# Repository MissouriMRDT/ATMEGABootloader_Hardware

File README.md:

# ATMEGABootloader_Hardware
A bootloader shield to flash an ATMEGA328 on an arduino

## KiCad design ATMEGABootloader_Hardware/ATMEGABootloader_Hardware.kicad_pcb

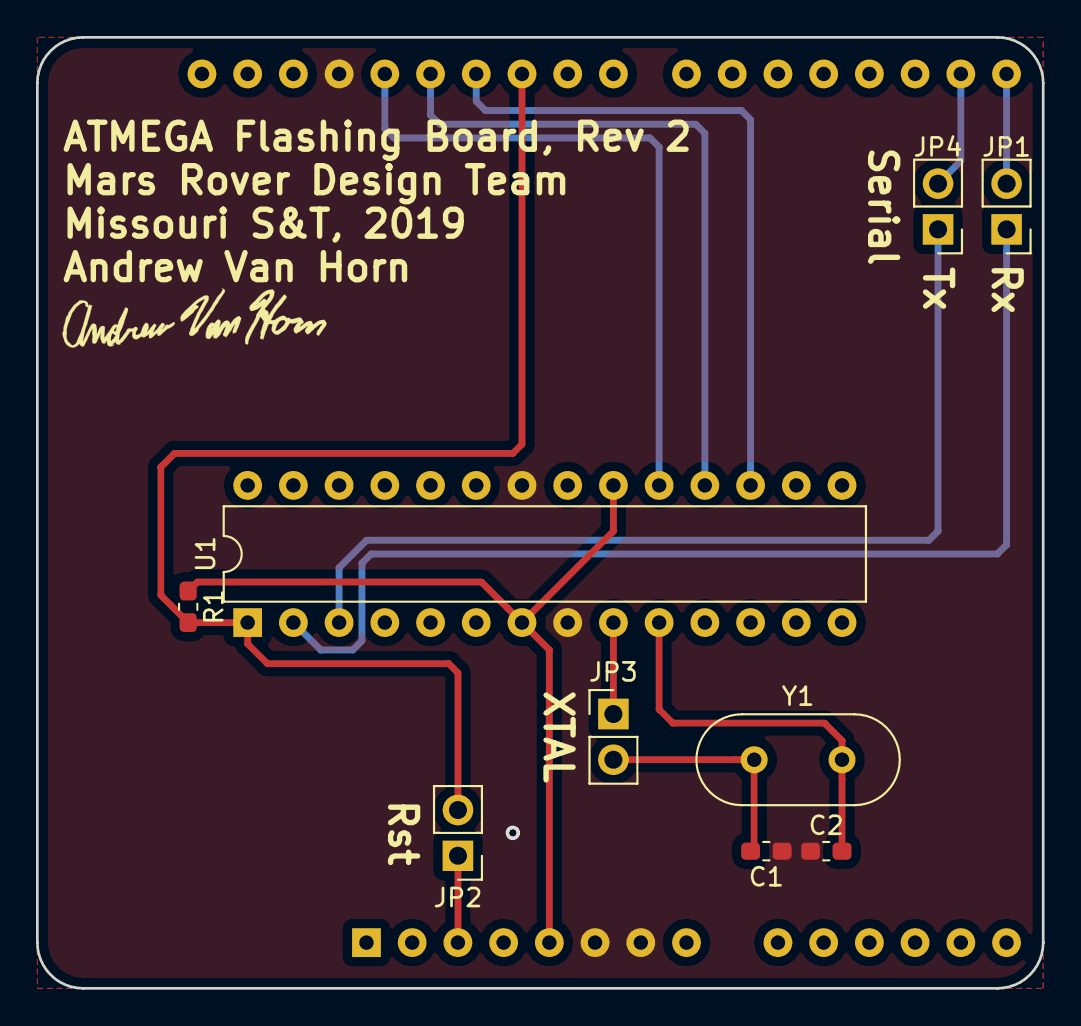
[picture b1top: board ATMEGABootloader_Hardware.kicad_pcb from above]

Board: 2 copper layers, 55.9 x 52.8 mm, 10 parts (1 on the bottom side), 14 nets.

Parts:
A1: Arduino_UNO_R3
C1, C2: 20pF; C_0603_1608Metric_Pad1.05x0.95mm_HandSolder
JP1, JP2, JP3, JP4: Jumper; PinHeader_1x02_P2.54mm_Vertical
R1: 10k; R_0603_1608Metric_Pad1.05x0.95mm_HandSolder
U1: ATmega328-PU; DIP-28_W7.62mm
Y1: 16MHz; Crystal_HC49-U_Vertical

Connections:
+5V: A1.5, R1.1, U1.7, U1.20
D11: A1.26, U1.17
D12: A1.27, U1.18
D13: A1.28, U1.19
GND: A1.6, A1.7, A1.29, C1.1, C2.1, U1.8, U1.22
unnamed: A1.3, JP2.1
unnamed: C1.2, JP3.2, Y1.1
unnamed: C2.2, U1.10, Y1.2
unnamed: JP1.1, U1.2
unnamed: JP3.1, U1.9
unnamed: JP4.1, U1.3
Rst: A1.25, JP2.2, R1.2, U1.1
Rx: A1.15, JP1.2
Tx: A1.16, JP4.2

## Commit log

2019-02-28 created schematic
2019-02-28 began layout
2019-02-28 did silkscreen
2019-05-18 Added gerbs
2020-06-01 Fixed RST routing and re generated gerbs
2020-06-01 Added BOM
2020-06-01 rerouted reset track
